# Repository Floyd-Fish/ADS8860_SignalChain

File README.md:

# ADS8860-EVM

ADS8860精密ADC信号链设计评估板

文章链接:  https://www.emoe.xyz/archives/1457

## 文件说明

- KiCad Files : KiCad设计文件  
- LTSpice Simulation : LTSpice仿真文件  
- ADS8860_Gerber.zip : KiCad导出Gerber文件,可直接加工

未完待续。

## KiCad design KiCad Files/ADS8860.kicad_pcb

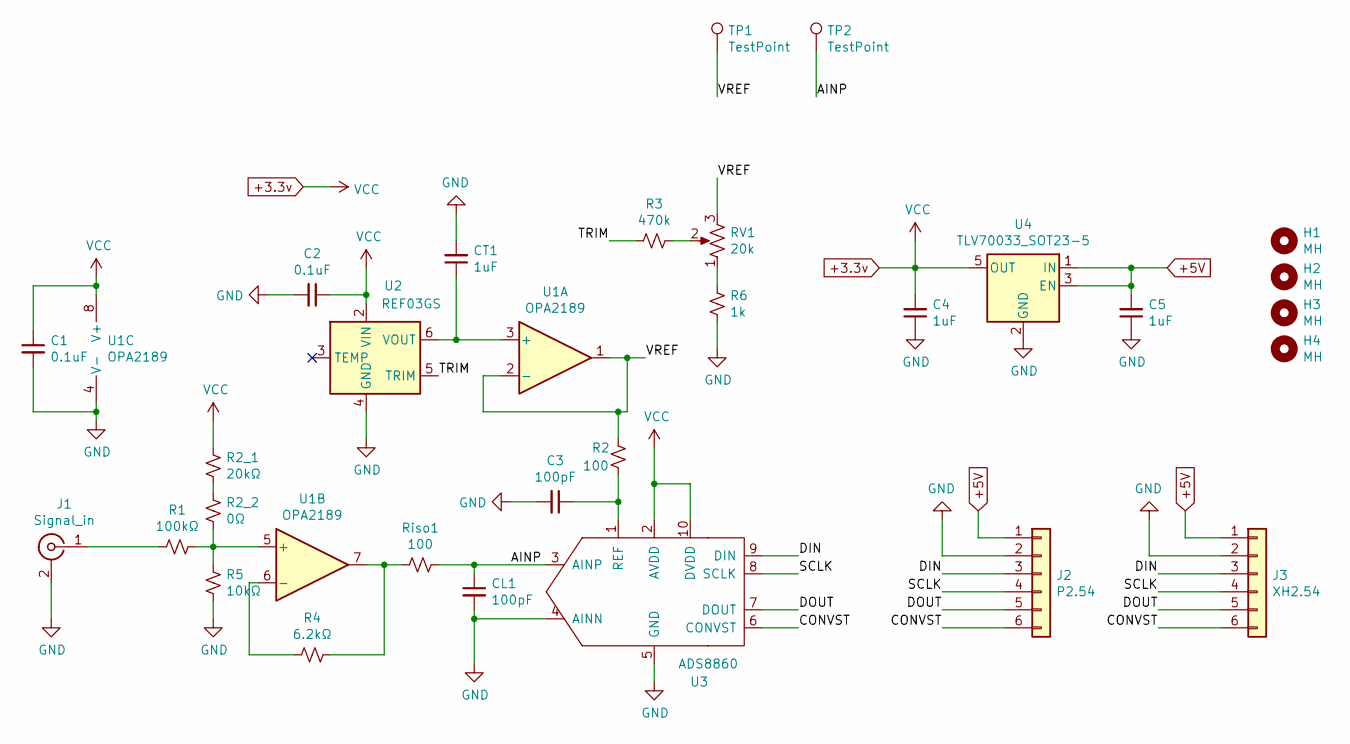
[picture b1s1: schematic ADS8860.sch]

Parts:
C1, C2: 0.1uF; C_0603_1608Metric
C3: 100pF; C_0603_1608Metric
C4, C5: 1uF; C_0603_1608Metric
CL1: 100pF; C_0603_1608Metric
CT1: 1uF; C_0603_1608Metric
H1, H2, H3, H4: MH; MountingHole_2.2mm_M2_Pad_Via
J1: Signal_in; SMA_Amphenol_132291_Vertical
J2: P2.54; PinHeader_1x06_P2.54mm_Vertical
J3: XH2.54; JST_XH_B6B-XH-A_1x06_P2.50mm_Vertical
R1: 100kΩ; R_0603_1608Metric
R2: 100; R_0603_1608Metric
R2_1: 20kΩ; R_0603_1608Metric
R2_2: 0Ω; R_0603_1608Metric
R3: 470k; R_0603_1608Metric
R4: 6.2kΩ; R_0603_1608Metric
R5: 10kΩ; R_0603_1608Metric
R6: 1k; R_0603_1608Metric
RV1: 20k; Potentiometer_Bourns_TC33X_Vertical
Riso1: 100; R_0603_1608Metric
TP1, TP2: TestPoint; TestPoint_THTPad_1.5x1.5mm_Drill0.7mm
U1: OPA2189; SOIC-8_3.9x4.9mm_P1.27mm
U2: REF03GS; SOIC-8_3.9x4.9mm_P1.27mm
U3: ADS8860; VSSOP-10_3x3mm_P0.5mm
U4: TLV70033_SOT23-5; SOT-23-5

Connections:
+3.3v: C1.1, C2.1, C4.2, R2_1.2, U1.8 (V+), U2.2 (VIN), U3.2 (AVDD), U3.10 (DVDD), U4.5 (OUT)
+5V: C5.2, J2.1, J3.1, U4.1 (IN), U4.3 (EN)
/AINP: CL1.1, Riso1.1, TP2.1, U3.3 (AINP)
/CONVST: J2.6, J3.6, U3.6 (CONVST)
/DIN: J2.3, J3.3, U3.9 (DIN)
/DOUT: J2.5, J3.5, U3.7 (DOUT)
/SCLK: J2.4, J3.4, U3.8 (SCLK)
/TRIM: R3.2, U2.5 (TRIM)
/VREF: R2.1, RV1.3, TP1.1, U1.1, U1.2 (-)
GND: C1.2, C2.2, C3.2, C4.1, C5.1, CL1.2, CT1.2, J1.2 (Ext), J2.2, J3.2, R5.2, R6.1, U1.4 (V-), U2.4 (GND), U3.4 (AINN), U3.5 (GND), U4.2 (GND)
unnamed: C3.1, R2.2, U3.1 (REF)
unnamed: CT1.1, U1.3 (+), U2.6 (VOUT)
unnamed: J1.1 (In), R1.2
unnamed: R1.1, R2_2.1, R5.1, U1.5 (+)
unnamed: R2_1.1, R2_2.2
unnamed: R3.1, RV1.2
unnamed: R4.1, Riso1.2, U1.7
unnamed: R4.2, U1.6 (-)
unnamed: R6.2, RV1.1

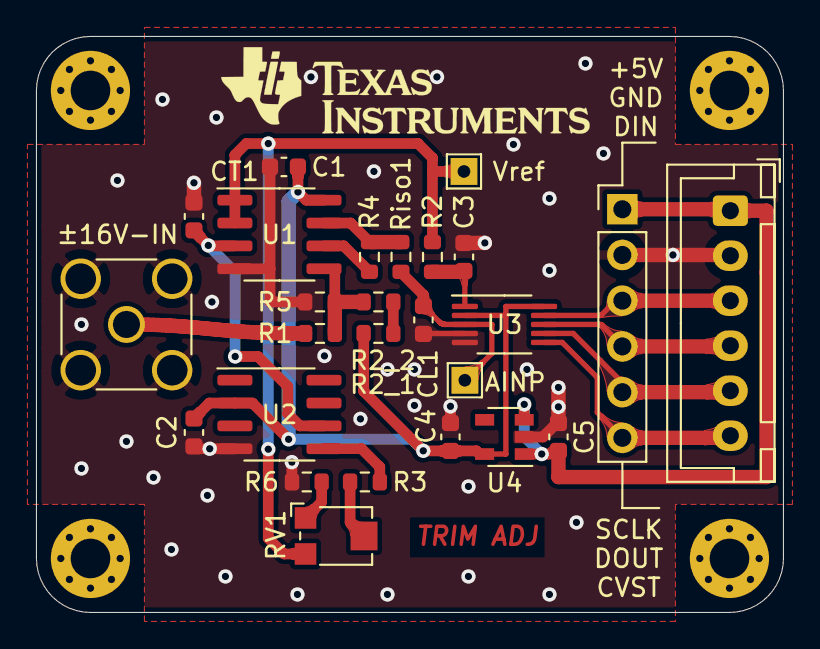
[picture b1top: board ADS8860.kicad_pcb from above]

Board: 2 copper layers, 41.5 x 32.0 mm, 30 parts (0 on the bottom side), 19 nets.

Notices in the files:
KiCad Files/ADS8860.kicad_pcb:
Copyright©Floydfish
KiCad Files/ADS8860.sch:
Copyright@Floydfish
